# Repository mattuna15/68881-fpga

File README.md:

# MC68881/2 FPGA Core

## Overview
A VHDL implementation of a Motorola MC68881/MC68882-compatible floating-point
coprocessor targeting Xilinx 7-series and UltraScale+ FPGAs. The design implements
the full MC68881 instruction set including all arithmetic, transcendental,
program-control, system-control, and packed-decimal operations. It uses
DSP-pipelined sequential FP units for the core arithmetic datapath with
multi-cycle path constraints for timing closure at 50 MHz.

Hardware-verified on an Alinx AXU3EG board (Zynq UltraScale+ ZU3EG) via the
AXI4-Lite wrapper at 100 MHz bus / 50 MHz FPU, with end-to-end tests covering
arithmetic, transcendental, exponential, and logarithmic operations.

## Features
- **Full instruction set**: FADD, FSUB, FMUL, FDIV, FSQRT, FMOD, FREM, FSCALE,
  FSGLDIV, FSGLMUL, FABS, FNEG, FINT, FINTRZ, FGETEXP, FGETMAN, FTST, FCMP.
- **Lite mode** (`fpu_lite_g => true`): MC68040 hardware subset -- keeps 11 ALU
  ops (ADD/SUB/MUL/DIV/SQRT/CMP/ABS/NEG/INT/INTRZ/TST) plus control/move ops.
  Removes trig engine, sglops unit, and modrem post-processing via VHDL generate
  blocks; stubs out GETEXP/GETMAN inline. Estimated ~57-60% LUT savings (pending
  synthesis verification). Unsupported ops return zero in 1 cycle.
- **Transcendental engine**: FSIN, FCOS, FTAN, FSINCOS, FASIN, FACOS, FATAN,
  FATANH, FSINH, FCOSH, FTANH, FETOX, FETOXM1, FTWOTOX, FTENTOX, FLOGN,
  FLOGNP1, FLOG2, FLOG10. BRAM coefficient ROM with Horner polynomial
  evaluation, table-assisted range reduction (ATAN, LOG), Cody-Waite
  argument reduction (trig), and FPSP-derived 2^(J/64) EXP decomposition
  with minimax degree-6 polynomial.
- **Data movement**: FMOVE (all formats including packed decimal `.P`),
  FMOVEM (register lists and control registers), FMOVECR (ROM constants).
- **Program control**: FScc, FBcc, FDBcc, FTRAPcc, FNOP with BSUN trap gating.
- **MC68882 mode** (`fpu_version_g => FPU_68882`): Pin-compatible 68882 variant
  with larger FSAVE frames (idle $0038/14W, busy $00D4/53W), pending instruction
  pipeline (accepts a second cpGEN while the first is executing; auto-launches on
  completion), and NULL response during CIR_EXECUTE for reduced CPU stalls.
  FRESTORE accepts both 68881 and 68882 format words for migration compatibility.
  Default is FPU_68881 for backward compatibility.
- **System control**: FSAVE/FRESTORE with Null/Idle/Busy frame support (45-word
  68881 / 53-word 68882 Busy frame with full sub-unit save/restore hierarchy).
- **IEEE 754 compliance**: NaN propagation (SNaN/QNaN discrimination, payload
  preservation), infinity handling, signed zero, gradual underflow, all four
  rounding modes (nearest, zero, +inf, -inf), single/double/extended precision.
- **Exception handling**: Per-operation FPSR exception policies, FPCR trap
  enable, accrued exception accumulation.
- **Dual host interface**: Two operating modes over the same 5-bit address space:
  - **CIR dialog** -- authentic AN-947 coprocessor protocol with internal FP register
    file, hardware format conversion, and command/response/operand dialog (for M68020/030)
  - **Peripheral (register-mapped)** -- direct OPA/OPB/OPSEL/RES register access for
    any host CPU (ARM, RISC-V, soft-core) as a standalone FPU compute engine
  - Mode selected by writing bit 0 of address 13 (1=CIR, 0=peripheral); CIR is
    default on reset, matching real MC68881 behaviour
- **SoC wrappers**: AXI4-Lite and Wishbone B4 slave wrappers with clock domain
  crossing (toggle handshake CDC), DSACK timeout protection, and interrupt output.
  Enable direct integration into Xilinx AXI or RISC-V Wishbone SoC interconnects.

## Utilization (Xilinx Artix-7 200T, post-place)

| Resource | Full | Lite (`fpu_lite_g`) | Available | Full % | Lite % |
|----------|------|---------------------|-----------|--------|--------|
| Slice LUTs | 59,919 | 37,380 | 133,800 | 44.78% | 27.94% |
| Registers | 14,087 | 7,030 | 267,600 | 5.26% | 2.63% |
| Block RAM | 10.5 tiles | 0 | 365 | 2.88% | 0% |
| DSP48E1 | 34 | 18 | 740 | 4.59% | 2.43% |

*Non-incremental synthesis + implementation, Vivado 2025.2, `xc7a200tfbg676-1`. Date: 2026-03-27.
50 MHz target clock. MC68882 mode enabled (`fpu_version_g => FPU_68882`). Includes
FPSP-derived EXP 2^(J/64) decomposition with minimax degree-6 polynomial (EXPTBL
64-entry BRAM), LOG reciprocal table (avoids FP division), TWOTOX/TENTOX direct
reduction, table-assisted ATAN/LOG, Cody-Waite trig, CIR coprocessor interface,
full exception dialog paths, undocumented FMOVECR ROM constants, pending instruction
pipeline, and graphics framebuffer support. Lite figures are from 2026-03-21 (pre-
efficiency changes, trig engine excluded by generate block).*

### Timing
- Target clock: **50 MHz** (20.0 ns period) — 2× the original MC68881 max (25 MHz).
- Multi-cycle path constraints on sequential FP units, trig engine hold states,
  format conversion paths (operand staging, MOVE dispatch, LOG exponent conversion,
  FP register file to exception destinations).
- Packed decimal encode pipeline: 3-stage split (exponent extraction → DSP multiply
  → scale computation) with pipelined DSP48E1 input.
- Post-route WNS: **+0.272 ns** at 50 MHz (timing met). No hold violations.

### Target device compatibility
The design fits on several FPGA families. With `fpu_lite_g => true` (MC68040
hardware subset: 11 ALU ops, no trig/sglops/modrem), the core uses 37,380 LUTs
/ 18 DSPs / 0 BRAM:

| Device | LUTs | DSPs | Full fit? | Lite fit? |
|--------|------|------|-----------|-----------|
| Xilinx Artix-7 200T | 133,800 | 740 | Yes (45%) | Yes (28%) |
| Xilinx Artix-7 100T | 63,400 | 240 | Tight (95%) | Yes (59%) |
| Xilinx Zynq UltraScale+ ZU3EG | ~71,000 | 360 | Yes (~84%) | Yes (~53%) |
| Intel Cyclone V 5CEBA7 | 150,720 ALMs | 156 | Yes | Yes |
| Intel Cyclone V SE 5CSEBA6 (MiSTer DE10-Nano) | 41,910 ALMs | 112 | No (~75%) | Yes (~45%) |

All RTL is VHDL-93 compatible and vendor-portable (inferred DSP/BRAM, no Xilinx
IP cores). The source is VHDL-93 compatible (verified via `ghdl --std=93`) and
should synthesize directly in Quartus 17+ (as used by MiSTer). Verify with `scripts/check_vhdl93.sh`.
Porting requires XDC-to-SDC constraint conversion and minor DSP inference
adjustments.

**MiSTer note:** The DE10-Nano's Cyclone V SE has 41,910 ALMs (each ALM roughly
maps to 2 Xilinx LUTs, giving ~84K LUT-equivalent). The full FPU (60K LUTs /
34 DSPs) exceeds ALM capacity but fits within the 112 DSP budget. Lite mode
(37K LUTs ≈ ~19K ALMs, 18 DSPs, 0 BRAM) should fit comfortably. These are rough
estimates; actual Quartus ALM counts may differ from Xilinx LUT counts due to
architectural differences.

## Architecture

```
mc68881_top                     Bus interface, format converters, FMOVECR ROM
├── alu_inst (mc68881_alu)      Opcode dispatch, shared FP unit mux
│   ├── trig_inst               Transcendental engine (generate: not fpu_lite)
│   ├── divrem_inst             Radix-4 SRT division, FSQRT
│   │   └── modrem_post         FMOD/FREM post-processing (generic: enable_modrem_post)
│   ├── sglops_inst             FSCALE, FSGLDIV, FSGLMUL (generate: not fpu_lite)
│   ├── alu_mul_inst            Shared 64×64 sequential multiplier (DSP48E1 cascade)
│   └── alu_add_inst            Shared 67-bit sequential adder/subtractor
└── packed_unit_inst            Packed-decimal BCD encode/decode (uses shared mul/add)
```

The ALU dispatches to **exactly one** consumer at a time. The trig unit runs
concurrently and has its own dedicated FP units. The ALU's mul and add instances
are **shared** between the ALU's own FADD/FSUB/FMUL path, the modrem post-processing
path, and the packed-decimal unit — saving ~5,300 LUTs and 32 DSPs vs. dedicated
instances per consumer.

## Repository layout
- `src/` — RTL sources (10 files, ~11.4K lines)
  - `mc68881_pkg.vhd` — Types, constants, FP80 utility functions
  - `mc68881_top.vhd` — Top-level bus interface, format converters
  - `mc68881_alu.vhd` — ALU dispatcher, shared FP unit routing
  - `mc68881_trig_unit.vhd` — Transcendental engine (BRAM seed tables)
  - `mc68881_divrem_unit.vhd` — Division, square root, mod/rem
  - `mc68881_modrem_post_unit.vhd` — FMOD/FREM post-processing
  - `mc68881_fp80_mul_unit.vhd` — Sequential 64×64-bit FP80 multiplier
  - `mc68881_fp80_addsub_unit.vhd` — Sequential 67-bit FP80 adder/subtractor
  - `mc68881_sgl_ops_unit.vhd` — FSCALE, FSGLDIV, FSGLMUL
  - `mc68881_packed_decimal_unit.vhd` — Packed-decimal BCD conversion
- `wrappers/` — SoC bus wrappers
  - `mc68881_bus_bridge.vhd` — CDC toggle-handshake bridge + M68K bus cycle FSM
  - `mc68881_axilite_wrapper.vhd` — AXI4-Lite slave (instantiates bridge + FPU)
  - `mc68881_wishbone_wrapper.vhd` — Wishbone B4 slave (instantiates bridge + FPU)
  - `mc68881_wrapper.xdc` — ASYNC_REG + false path timing constraints for CDC bridge
  - `mc68881_ooc_timing.xdc` — Multicycle path constraints for OOC block design synthesis
- `src/vitis/` — Bare-metal C test apps for Xilinx Vitis (AXI-Lite hardware validation)
  - `mc68881_smoke_test.c` — Register read/write connectivity test (FPCR, FPIAR)
  - `mc68881_fsin_test.c` — FSIN computation test (sin(1.0), sin(0.0))
  - `mc68881_e2e_test.c` — End-to-end test with 15 vectors from GHDL testbench
- `validation/NeXT-68040/` — NeXT 68040LC system emulator (Turbo ROM boot, interactive `NeXT>` monitor, hardware FPU via FSAVE/FRESTORE frame translation, DisplayPort output)
- `validation/hello_world/` — M68K emulator + hardware FPU validation (Musashi, F-line trapping, ROM boot, USB keyboard)
- `validation/kicad/` — Validation PCB: MC68SEC000 + QMTECH Artix-7 + original MC68881FN (KiCad 8, Gerbers in `output/`)
- `src/vitis/roms/` — 68000 BIOS ROM source (assembler, disassembler, monitor with FPU support)
- `tb/` — VHDL-2008 self-checking testbenches (14 files, ~8.5K lines)
- `docs/` — Implementation plan, timing notes, reference documentation
- `verilog/` — Auto-generated Verilog conversion; `verilog/fpu_lite/` has the lite-mode variant (see [verilog/README.md](verilog/README.md))
- `scripts/` — Test runner, golden vector generator, implementation TCL
- `.github/workflows/ghdl.yml` — CI: GHDL analysis + 4 testbench runs
- `.githooks/pre-push` — Pre-push GHDL regression gate

## Running simulations
Use a VHDL-2008 capable simulator (GHDL 5.1.1+ recommended). The repo includes
a test script that runs the full regression suite:

```powershell
scripts/run_tests.ps1
```

The script uses `GHDL_EXE` if set, otherwise defaults to
`C:\code\ghdl-mcode-5.1.1-mingw64\bin\ghdl.exe` and finally `ghdl` on PATH.

### CI testbenches
The GitHub Actions workflow runs these testbenches on every push:
- `tb_mc68881_alu` — Arithmetic, NaN/infinity, transcendental, special values
- `tb_mc68881_alu_lite` — Lite-mode (`fpu_lite => true`): kept ops + removed ops return zero
- `tb_mc68881_top` — Bus interface, format conversions, FPSR/exception checks
- `tb_mc68881_ea_cycles` — Effective address cycle count tables
- `tb_mc68881_cycle_counts` — Instruction cycle timing verification

### Golden vectors
- Generator: `scripts/gen_golden_vectors.py` (mpmath-based FP80 rounded constants).
- Checked-in package: `tb/mc68881_golden_vectors_pkg.vhd`.
- Compile order: `mc68881_golden_vectors_pkg.vhd` must be analyzed before `tb_mc68881_alu.vhd`.

### Pre-push hook
The pre-push hook in `.githooks/pre-push` runs GHDL analysis and the ALU/top
testbenches. To enable hooks locally:

```sh
git config core.hooksPath .githooks
```

## Synthesis and LUT reporting
Use non-incremental synthesis for area/LUT comparisons. Incremental reuse can mask
RTL changes and produce stale utilization numbers.

```tcl
set_property AUTO_INCREMENTAL_CHECKPOINT 0 [get_runs synth_1]
set_property INCREMENTAL_CHECKPOINT "" [get_runs synth_1]
reset_run synth_1
launch_runs synth_1
```

For hotspot analysis, generate hierarchical utilization from the synthesized checkpoint:

```tcl
open_checkpoint mc68881_top.dcp
report_utilization -hierarchical -hierarchical_depth 10 -file mc68881_top_util_hier.rpt
```

### Transcendental accuracy
The transcendental engine achieves 30–64 bits of accuracy across operations,
verified by the torture testbench (357 self-checking tests):

| Operation | Typical accuracy | Method |
|-----------|-----------------|--------|
| SIN, COS, TAN | 30–40 bits | Cody-Waite argument reduction, table-assisted seed refinement |
| ASIN, ACOS, ATAN | 55–62 bits | Table-assisted polynomial (64 BRAM entries) |
| EXP, ETOXM1 | ~40–54 bits | FPSP 2^(J/64) decomposition, minimax degree-6 Horner |
| TWOTOX, TENTOX | ~47 bits | Direct k=nint(x) reduction, degree-9 Taylor |
| LOG, LOG2, LOG10 | ~54 bits | Table-assisted range reduction, reciprocal multiply |
| SINH, COSH | 30–50 bits | Dedicated odd/even Taylor polynomials |
| TANH | ~32–42 bits | Via EXP64 pipeline |

## Transcendental architecture guardrails
- The transcendental engine uses BRAM-style synchronous reads via
  `ST_SEED_READ -> ST_SEED_READ_WAIT -> ST_SEED_READ_LATCH`.
- Coefficient BRAM ROM stores 6 sets × 10 coefficients (EXP/LOG/ATAN/SINH/COSH/EXP64);
  requires 2-cycle read latency: `POLY_INIT` → `INIT_WAIT` → `MUL_PREP`.
- EXP64 BRAM (64 entries of 2^(J/64)) uses same synchronous read pattern:
  `ST_EXP64_N_POST` → `ST_EXP64_TABLE_WAIT` → `ST_EXP64_TABLE_LATCH`.
- LOG reciprocal table (64 entries of 1/c_i) reads alongside c_i and ln(c_i)
  on the same BRAM address — no extra read cycle needed.
- Do **not** replace synchronous reads with combinational table indexing — it
  breaks BRAM inference and increases LUT usage sharply.
- Validate architecture changes with non-incremental synth utilization reports.

## Verilog conversion
The VHDL sources can be converted to Verilog via `ghdl --synth` for use with
Verilator or other Verilog-only toolchains. The pre-push hook regenerates these
automatically. To convert manually:

```powershell
powershell -ExecutionPolicy Bypass -File scripts/convert_to_verilog.ps1
```

Output goes to [`verilog/`](verilog/). A lite-mode variant (`fpu_lite_g => true`)
is also generated into `verilog/fpu_lite/`. **These files are supplied as-is for
information only — no guarantee of correctness is made and no tests are run on
the converted code.** The VHDL sources remain the authoritative implementation.

## Block design integration (Xilinx Vivado)

The AXI-Lite wrapper can be added to a Vivado block design as a custom RTL module.
Both XDC constraint files must be included with the IP:

- `mc68881_wrapper.xdc` — CDC false paths for the toggle-handshake bridge
- `mc68881_ooc_timing.xdc` — Multicycle path constraints scoped to `*/u_fpu/`

The OOC timing constraints are adapted from `mc68881_top.xdc` for the wrapper
hierarchy. Key differences from standalone synthesis:
- All `get_pins` patterns use `*/u_fpu/` prefix
- `move_cfg_decoded_reg` (record type) is optimized away in OOC synthesis;
  constraints target `move_cfg_reg_reg` instead
- `packed_unit_inst` is inside generate block `packed_engine_full_g`
- CDC `get_cells` filters include `&& IS_SEQUENTIAL` to avoid matching LUT cells

Verified on Xilinx Zynq UltraScale+ ZU3EG (AXU3EG board) with Vivado 2025.2:
post-route WNS **+1.186 ns** at 100 MHz AXI / 50 MHz FPU (MC68882 mode).
Board design utilization: 64,014 LUTs (91%), 15,206 registers, 8 BRAM tiles,
34 DSPs. All timing constraints met with no hold violations.

### Vitis hardware test apps

The `src/vitis/` directory contains standalone C test applications for
validating the FPU over AXI-Lite. These target the Xilinx Vitis bare-metal BSP.

| Test | What it checks |
|------|----------------|
| `mc68881_smoke_test.c` | Bus connectivity: write/readback of FPCR and FPIAR |
| `mc68881_fsin_test.c` | FPU operation: sin(1.0) and sin(0.0) with result printout |
| `mc68881_e2e_test.c` | 17 test vectors: ADD, SUB, MUL, DIV, SQRT, SIN, COS, TAN, ETOX, LOGN, FMOVECR, pi/3 |

All tests include `0xFFFFFFFF` bus fault detection, timeout handling with status
reporting, and non-zero exit on failure for use in automated test flows.

Set `MC68881_BASE` to match your address map (default `0x80000000`).

### M68K emulator validation (CIR + peripheral modes)

The [`validation/hello_world/src/README.md`](validation/hello_world/src/README.md) project runs a full
M68K emulator (Musashi) on the ARM core, trapping F-line FPU instructions and
executing them on the hardware FPU over AXI-Lite. The test suite validates
**both** operating modes:

**Peripheral mode** (7 + 5 tests) -- the FPU as a standalone compute engine.
The emulator's F-line handler converts operands to FP80 in software, writes them
to the OPA/OPB registers, triggers execution via OPSEL, and reads results from
RES. No CIR involvement:

```c
fpu_wr(OFF_CIR_MODE, 0);              // ensure peripheral mode
fpu_load_opa(a);                       // write FP80 operand A
fpu_load_opb(b);                       // write FP80 operand B
fpu_wr(OFF_OPSEL, OPSEL(FPOP_ADD));   // trigger FADD
while (!(fpu_rd(OFF_STATUS) & 1)) {}  // poll for completion
result = fpu_read_res();               // read FP80 result
```

**CIR dialog mode** (7 tests) -- the authentic AN-947 coprocessor protocol.
The host writes a Command + OpWord to start a dialog, the FPU responds with
transfer primitives, the host feeds operand words through the CIR Operand
register, and the FPU stores results in its internal FP register file (FP0-FP7):

```c
cir_wr(OFF_CIR_RESPONSE, 1);           // ensure CIR mode
cir_wr(OFF_CIR_COMMAND, cmd);          // operation + format + register
cir_wr(OFF_CIR_OPWORD,  CIR_OPWORD_CPGEN);  // triggers FSM
resp = cir_poll_response();            // → 0x9604 (AN-947: transfer CPU→FPU, 4 bytes)
cir_wr(OFF_CIR_OPERAND, 42);          // write source operand
cir_wait_null();                       // dialog complete; result in FP register
```

The two modes share a 5-bit address space with overlapping registers (addresses
1, 4, 5, 7, 8, 14). A mode flag at address 13 gates the decode: CIR mode is
default on reset. See the [validation README](validation/hello_world/src/README.md)
for the full address map, protocol details, and code examples.

19/19 tests pass: 7 peripheral smoke + 7 CIR dialog + 5 Musashi integration.

### BIOS ROM boot mode

The default build boots a 68000 BIOS ROM with an interactive monitor, built-in
assembler (CODE68K), and disassembler (DCODE68K). Character I/O is routed through
MC68901 MFP emulation (ARM UART ↔ emulated MFP USART) and rendered to a text
framebuffer displayed on the PS DisplayPort output (1280×720@60Hz).

USB keyboards and mice are supported via the ZynqMP DWC3 xHCI host controller:
- **Keyboard**: HID boot-protocol, Caps Lock/Num Lock with LED feedback, feeds
  ASCII into the MFP RX buffer alongside ARM UART input
- **Mouse**: HID boot-protocol, buttons + relative/absolute position tracking,
  accessible via memory-mapped I/O at `$FD0050` and TRAP #15 (D0=26/27/28)
- Automatic hub traversal (up to 3 levels) — works with keyboards and mice
  behind USB hubs, including combo devices with built-in hubs

The assembler and disassembler support all MC68881 FPU instructions:
- **39 FPU mnemonics**: FMOVE through FMOVECR (all arithmetic, transcendental,
  data movement, and compare/test operations)
- **32 FBcc conditions**: FBEQ, FBGT, FBGE, FBLT, FBLE, FBGL, FBGLE, FBOGT,
  FBOGE, FBOLT, FBOLE, FBOGL, FBOR, FBUN, FBUEQ, FBUGT, FBUGE, FBULT,
  FBULE, FBNE, FBT, FBSF, FBST, FBSEQ, FBSNE, and negated variants
- **All format suffixes**: `.B`, `.W`, `.L`, `.S`, `.D`, `.X`, `.P`
- **Floating-point literals**: Decimal FP constants (e.g., `FADD.S #2.35,FP0`)
  with IEEE 754 conversion for `.S` (single), `.D` (double), and `.X` (extended)
- **FMOVE variants**: reg↔reg, mem↔reg, reg→mem, FMOVECR, FMOVE to/from
  FPCR/FPSR/FPIAR

The monitor supports Go (execute), single-step Trace, software Breakpoints
(up to 8), register dump (CPU + FPU), and memory inspect/modify. See the
[BIOS User Guide](docs/merlin2_bios.md) for full command reference and build
instructions.

The BIOS ROM source is in `validation/hello_world/src/roms/bios.s`. Build with:

```bash
vasmm68k_mot -Fbin -m68000 -o bios.bin bios.s
# Extract ROM section and convert to C header (see docs/merlin2_bios.md)
```

### Hardware validation output

E2e test run on AXU3EG (Zynq UltraScale+ ZU3EG), Vitis 2025.2:

```
Zynq MP First Stage Boot Loader
Release 2025.2   Mar  9 2026  -  17:13:45
PMU-FW is not running, certain applications may not be supported.
PMU Firmware 2025.2     Mar  9 2026   17:13:51
PMU_ROM Version: xpbr-v8.1.0-0

mc68881 e2e test (vectors from GHDL tb)
========================================
PASS ADD 3.7+2.4
PASS SUB -2.3-0.6
PASS MUL 3.7*2.4
PASS DIV 12.5/-0.7
PASS SQRT(9)
PASS SIN(1.0)
PASS SIN(1.1)
PASS SIN(-0.7)
PASS COS(-2.3)
PASS COS(0.3)
PASS TAN(0.9)
PASS ETOX(0.75)
PASS LOGN(1.25)
PASS SIN(0)
PASS SQRT(1)
PASS FMOVECR(pi)
PASS DIV(pi/3)
========================================
17 passed, 0 failed, 17 total
ALL TESTS PASSED
```

### FPU benchmarks

Standard floating-point benchmarks run on the M68K emulator with hardware FPU
(F-line trapping to FPGA), measured on AXU3EG at 100 MHz AXI / 50 MHz FPU:

**Whetstone** (NLOOP=10, exercises ADD/SUB/MUL/DIV/SQRT/SIN/COS/ATAN/LOG/EXP):
```
=== Whetstone Benchmark ===
M2 (array)... OK
M3 (proc array)... OK
M4 (conditionals)... OK
M6 (log/exp/sqrt)... OK
M7 (proc calls)... OK
M8 (trig)... OK

Passes: 10
Elapsed: 2191 ms
KWIPS: 4564
Whetstone complete.
```

**Savage** (2500 iterations of x = tan(atan(exp(ln(sqrt(x*x)))))), result should be 1.0):
```
=== Savage Benchmark ===
Result: 3FFE0000 FFFFFFFF FFFE54C8
Expect: 3FFF0000 80000000 00000000  (1.0)
Iterations: 2500
Elapsed: 210 ms
Done.
```

The Savage result (~0.999999999999994) shows ~6×10⁻¹⁵ accumulated rounding error
over 2500 iterations of 6 chained transcendental operations — reasonable for
64-bit extended precision.

Benchmark sources are in `validation/hello_world/src/roms/` (`savage.s`, `whetstone.s`).

### GCC example programs

The `toolchain/examples/` directory contains C programs compiled with the m68k-elf-gcc
cross-compiler and loaded via S-record transfer. Build with `.\build.ps1` (requires
Cygwin with m68k-elf-gcc).

| Program | Description | FPU? |
|---------|-------------|------|
| `hello.c` | Hello world (printf, TRAP I/O) | No |
| `fputest.c` | FPU arithmetic test (sin, cos, sqrt) | Yes |
| `fireworks.c` | Animated fireworks demo (physics + graphics) | Yes |
| `rtctest.c` | RTC date/time read/set, Timer C tick monitor | No |
| `mousetest.c` | USB mouse demo (crosshair cursor, click markers) | No |

**Mouse demo** (`mousetest.c`): Switches to 1280×720 graphics mode and renders a
green crosshair cursor that tracks the USB mouse. Left/right/middle clicks leave
coloured dot markers on the screen. A banner at the top displays the current X/Y
position and active buttons. Press any keyboard key to exit. Reads mouse state
directly from memory-mapped I/O at `$FD0050` (buttons, delta, absolute position).

## Validation PCB

The `validation/kicad/` directory contains a KiCad 8 project ("NextCuboid") for a
physical validation board that connects a real MC68SEC000 CPU to the QMTECH
Artix-7 200T core board running the FPGA FPU core, alongside an original 5V
MC68881FN for comparison testing. This is the first physical hardware validation
of the coprocessor interface — exercising real bus timing, level shifting, and
the CIR dialog protocol over actual copper.

### Board architecture

```
MC68SEC000FU20 (3.3V, 20 MHz)
    │
    ├── Coprocessor bus ──► SN74LVC8T245 level shifters (3.3V ↔ 5V)
    │                           │
    │                           ├──► MC68881FN (original 5V DIP/PLCC)
    │                           │
    │                           └──► QMTECH Artix-7 200T (mc68881_top)
    │
    └── Active-low control ──► 74LVC1G125 single-gate buffers
```

### Key components

| Component | Part | Role |
|-----------|------|------|
| CPU | MC68SEC000FU20 | 3.3V 68000-compatible bus master |
| FPGA FPU | QMTECH XC7A200T core board | Runs `mc68881_top` with bus bridge |
| Reference FPU | MC68881FN (original Motorola) | 5V DIP/PLCC, golden reference |
| Level shifters | SN74LVC8T245 (×5) | Bidirectional 3.3V ↔ 5V translation |
| Control buffers | 74LVC1G125 (×2) | Single-gate active-low signal translation |

The board uses dual QMTECH connectors (active main + active secondary headers)
and includes 4.7K pull-up resistors on open-drain/open-collector signals plus
100nF decoupling capacitors on all ICs. Gerber outputs are in
`validation/kicad/output/`.

PCB production sponsored by [PCBWay](https://www.pcbway.com) — thanks to them
for supporting this project.

## Status
All checklist items complete. See `docs/fpu-progress-checklist.md` for history.

## Documentation index

### Project documentation
| File | Description |
|------|-------------|
| [`docs/history.md`](docs/history.md) | Development history and changelog |
| [`docs/merlin2_bios.md`](docs/merlin2_bios.md) | Merlin2 BIOS monitor user guide |
| [`docs/trig_design.md`](docs/trig_design.md) | Transcendental engine architecture and algorithm design |
| [`docs/fpsp_comparison_checklist.md`](docs/fpsp_comparison_checklist.md) | FPSP (68040 FP software package) comparison checklist |
| [`docs/next68040_defect_checklist.md`](docs/next68040_defect_checklist.md) | NeXT 68040LC emulator defect/TODO tracker |
| [`docs/nextmach_boot_checklist.md`](docs/nextmach_boot_checklist.md) | NeXTMach kernel boot checklist |
| [`docs/merlin2_tasklist.md`](docs/merlin2_tasklist.md) | Merlin2 BIOS task list |
| [`docs/archive/fpu-progress-checklist.md`](docs/archive/fpu-progress-checklist.md) | Master checklist: implementation status (archived) |
| [`docs/archive/fmovecr_qemu_summary.md`](docs/archive/fmovecr_qemu_summary.md) | FMOVECR ROM constant cross-reference (archived) |
| [`docs/archive/qmtech_constraints_verification.md`](docs/archive/qmtech_constraints_verification.md) | XDC constraints verification for QMTECH board (archived) |

### Motorola / Atari reference manuals
| File | Description |
|------|-------------|
| [`docs/datasheets/MC68881UM.pdf`](docs/datasheets/MC68881UM.pdf) | MC68881/MC68882 User Manual (Motorola) |
| [`docs/datasheets/MC68881.PDF`](docs/datasheets/MC68881.PDF) | MC68881 datasheet |
| [`docs/datasheets/MC68040UM.pdf`](docs/datasheets/MC68040UM.pdf) | MC68040 User Manual (Motorola) |
| [`docs/datasheets/68881-tech-summary.pdf`](docs/datasheets/68881-tech-summary.pdf) | MC68881 Technical Summary |
| [`docs/datasheets/AN-0947_MC68881...pdf`](docs/datasheets/AN-0947_MC68881_Floating-Point_Coprocessor_as_a_Peripheral_in_a_M68000_System_%5BMotorola_1987_37p%5D.pdf) | AN-947: MC68881 as Peripheral in M68000 System |
| [`docs/datasheets/68881-programming.txt`](docs/datasheets/68881-programming.txt) | MC68881 programming reference notes |
| [`docs/datasheets/atari_sfp_en.pdf`](docs/datasheets/atari_sfp_en.pdf) | Atari SFP-004 programming by example |
| [`docs/datasheets/atari_68881_co-processor.pdf`](docs/datasheets/atari_68881_co-processor.pdf) | Atari MC68881 coprocessor board reference |

### Hardware reference
| File | Description |
|------|-------------|
| [`docs/datasheets/AXU3EG_User_Manual.pdf`](docs/datasheets/AXU3EG_User_Manual.pdf) | Alinx AXU3EG (Zynq UltraScale+ ZU3EG) board manual |
| [`docs/datasheets/QMTECH_XC7A200T-CORE-BOARD-V01-*.pdf`](docs/datasheets/) | QMTECH Artix-7 200T core board manual |
| [`docs/datasheets/MecbManual.pdf`](docs/datasheets/MecbManual.pdf) | MECB 68000 educational board manual |

### Design plans
| File | Description |
|------|-------------|
| [`docs/plans/2026-03-22-68040-emutos-variant.md`](docs/plans/2026-03-22-68040-emutos-variant.md) | MC68040 EmuTOS variant plan |
| [`docs/plans/2026-03-19-68882-upgrade.md`](docs/plans/2026-03-19-68882-upgrade.md) | MC68882 upgrade plan (pending pipeline, frame formats) |
| [`docs/plans/2026-03-03-s7-coprocessor-interface.md`](docs/plans/2026-03-03-s7-coprocessor-interface.md) | CIR coprocessor interface implementation plan |
| [`docs/plans/2026-02-28-packed-decimal-completion.md`](docs/plans/2026-02-28-packed-decimal-completion.md) | Packed decimal conversion completion plan |

### READMEs
| File | Description |
|------|-------------|
| [`validation/NeXT-68040/README.md`](validation/NeXT-68040/README.md) | NeXT 68040LC emulator: Turbo ROM boot, interactive monitor, hardware FPU on ZynqMP |
| [`validation/hello_world/src/README.md`](validation/hello_world/src/README.md) | Validation firmware: peripheral + CIR protocol, SFP004 benchmark |
| [`toolchain/README.md`](toolchain/README.md) | M68K GCC cross-compilation toolchain |
| [`toolchain/merlin-68k-toolchain/README.md`](toolchain/merlin-68k-toolchain/README.md) | Merlin2 68K toolchain (newlib, BSP) |

## License
See repository for license terms.

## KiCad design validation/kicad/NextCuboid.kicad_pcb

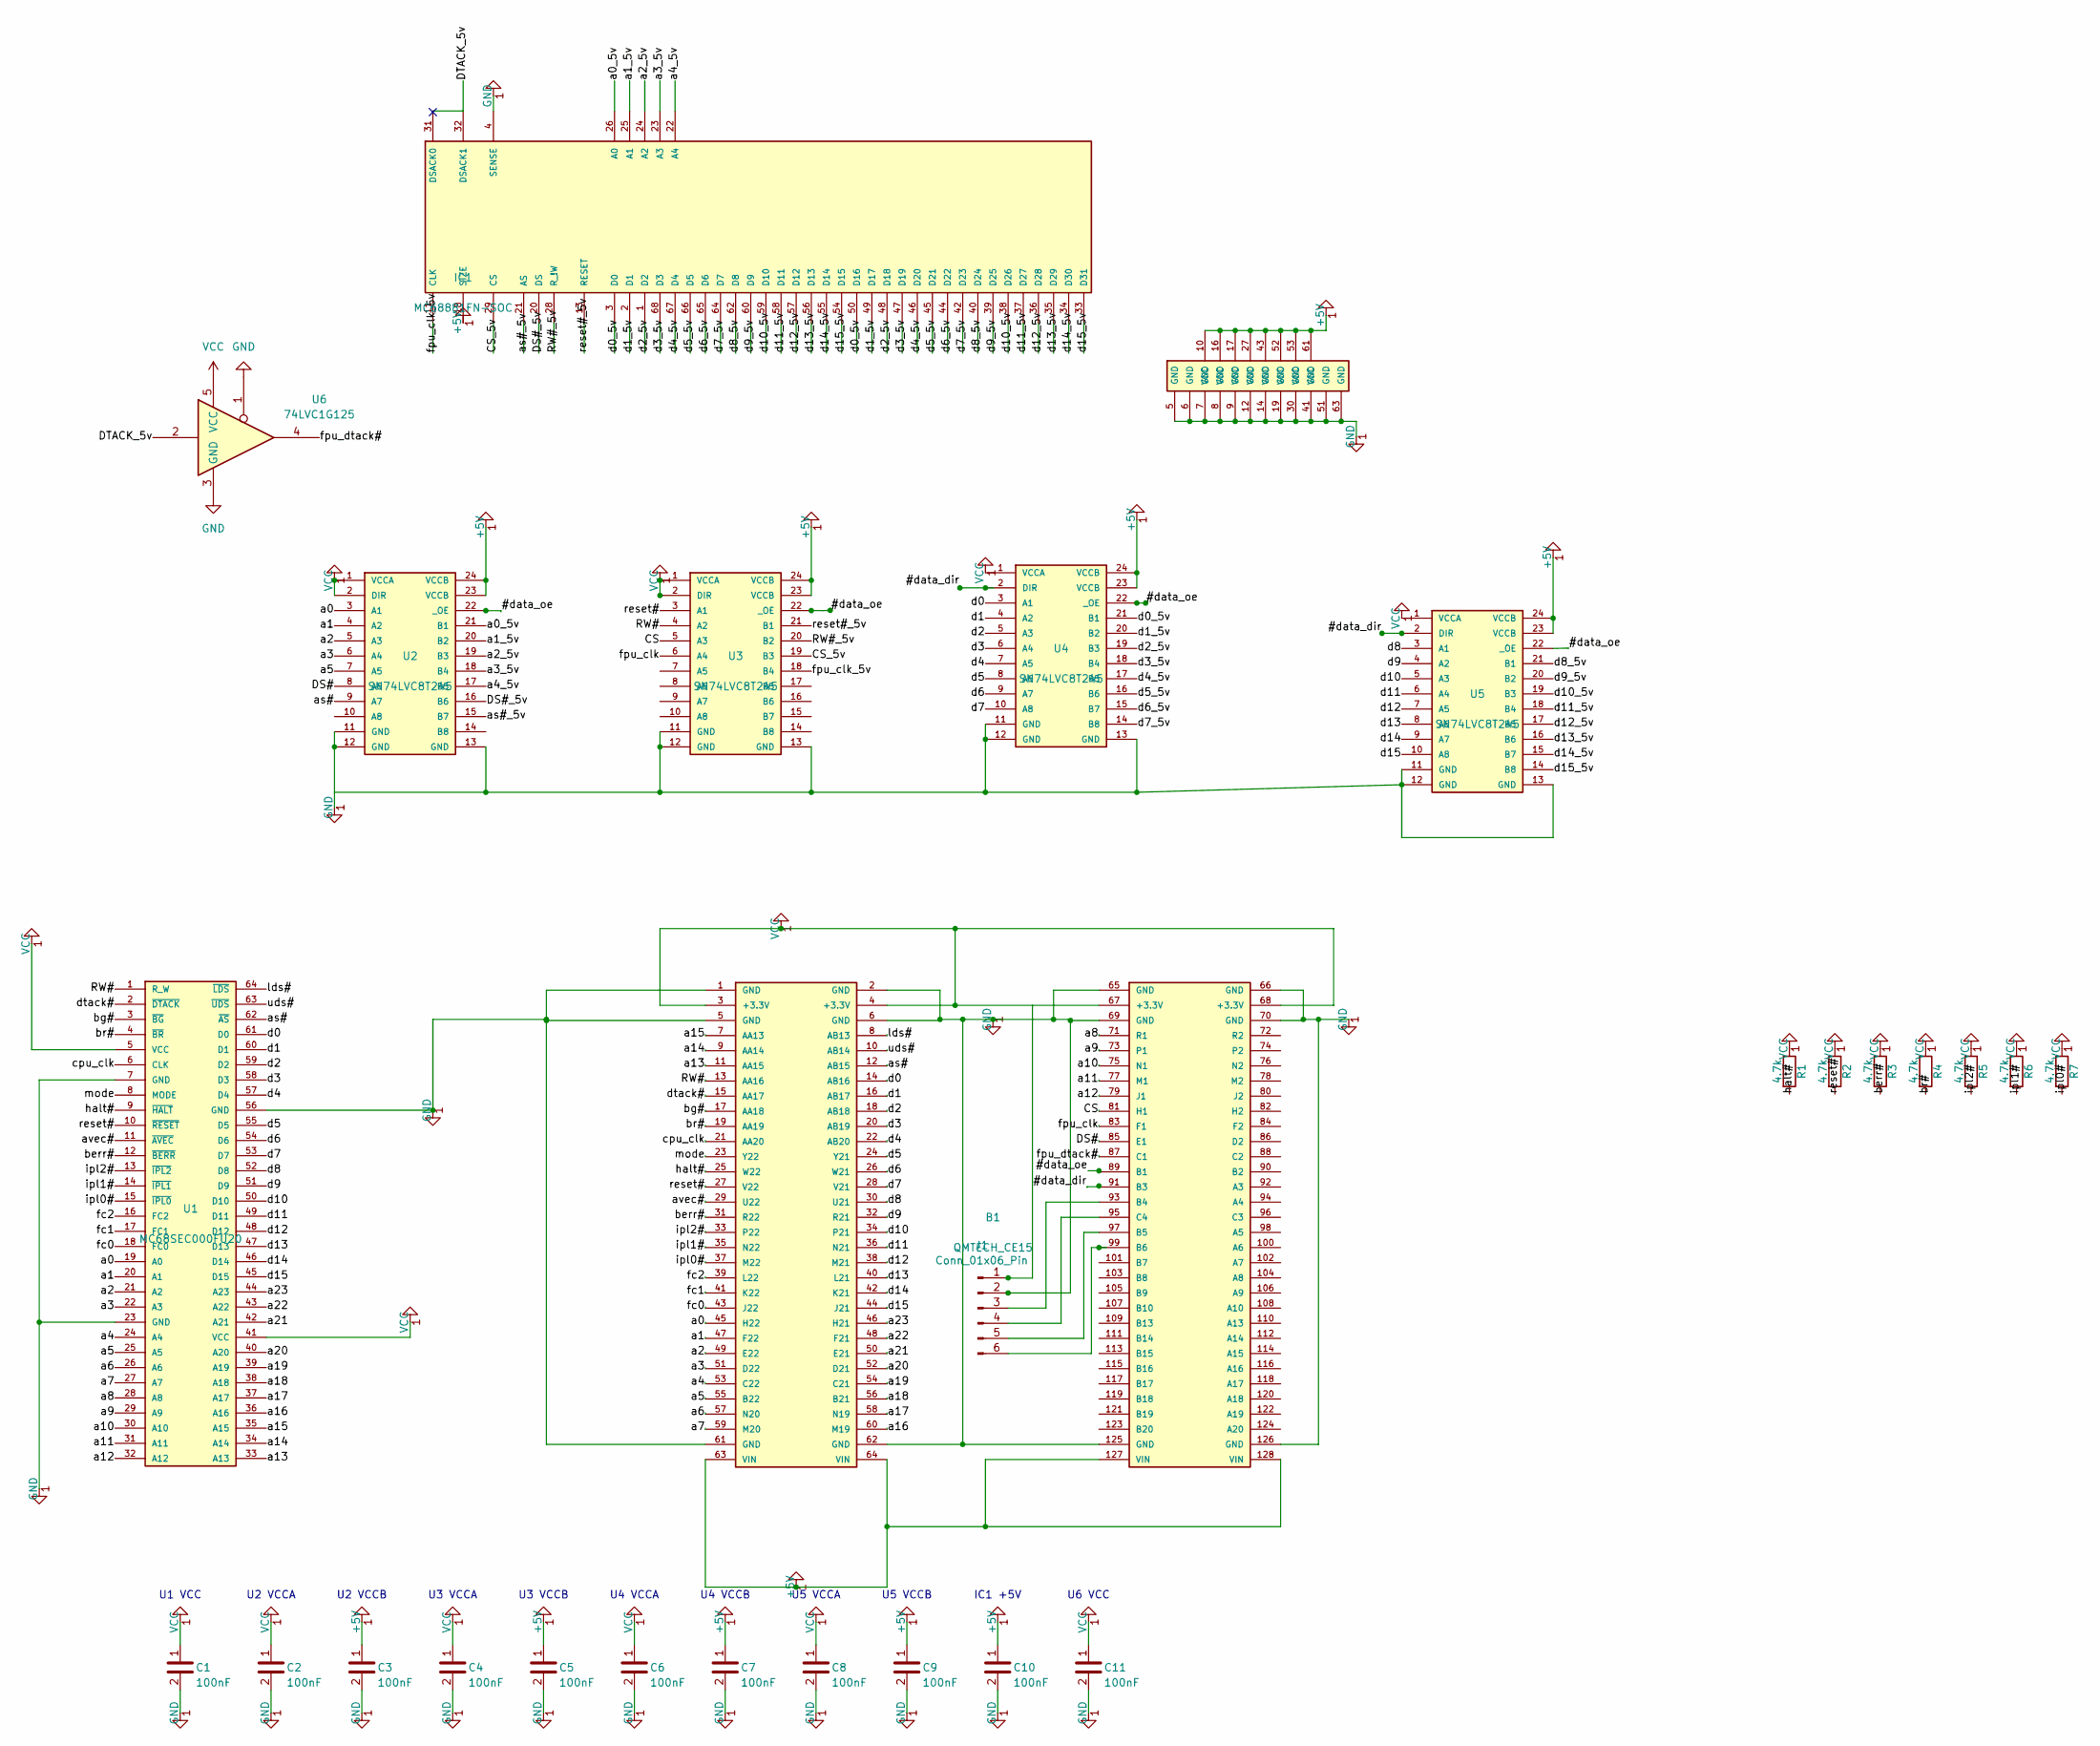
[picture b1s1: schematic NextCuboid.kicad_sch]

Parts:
B1: QMTECH_CE15; QMTECH_BOARD
C1, C2, C3, C4, C5, C6, C7, C8, C9, C10, C11: 100nF; C_Disc_D5.0mm_W2.5mm_P2.50mm
IC1: MC68881FN-SOC; PLCC68-S
J1: Conn_01x06_Pin; PinHeader_1x06_P2.54mm_Vertical
R1, R2, R3, R4, R5, R6, R7: 4.7k; R_Axial_DIN0207_L6.3mm_D2.5mm_P7.62mm_Horizontal
U1: MC68SEC000FU20; LQFP-64_L14.0-W14.0-P0.80-LS16.0-BL
U2, U3, U4, U5: SN74LVC8T245; DIP24L_BREAKOUT
U6: 74LVC1G125; SOT-23-5

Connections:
+5V: B1.63 (VIN), B1.64 (VIN), B1.127 (VIN), B1.128 (VIN), C3.1, C5.1, C7.1, C9.1, C10.1, IC1.10 (VCC), IC1.16 (VCC), IC1.17 (VCC), IC1.18 (SIZE), IC1.27 (VCC), IC1.43 (VCC), IC1.52 (VCC), IC1.53 (VCC), IC1.61 (VCC), U2.23 (VCCB), U2.24 (VCCB), U3.23 (VCCB), U3.24 (VCCB), U4.23 (VCCB), U4.24 (VCCB), U5.23 (VCCB), U5.24 (VCCB)
/#data_dir: U4.2 (DIR), U5.2 (DIR)
/#data_oe: B1.89 (B1), U2.22 (_OE), U3.22 (_OE), U4.22 (_OE), U5.22 (_OE)
/CS: B1.81 (H1), U3.5 (A3)
/CS_5v: IC1.29 (CS), U3.19 (B3)
/DS#: B1.85 (E1), U2.8 (A6)
/DS#_5v: IC1.20 (DS), U2.16 (B6)
/DTACK_5v: IC1.31 (DSACK0), IC1.32 (DSACK1), U6.2
/RW#: B1.13 (AA16), U1.1 (R_W), U3.4 (A2)
/RW#_5v: IC1.28 (R_!W), U3.20 (B2)
/a0: B1.45 (H22), U1.19 (A0), U2.3 (A1)
/a0_5v: IC1.26 (A0), U2.21 (B1)
/a1: B1.47 (F22), U1.20 (A1), U2.4 (A2)
/a1_5v: IC1.25 (A1), U2.20 (B2)
/a2: B1.49 (E22), U1.21 (A2), U2.5 (A3)
/a2_5v: IC1.24 (A2), U2.19 (B3)
/a3: B1.51 (D22), U1.22 (A3), U2.6 (A4)
/a3_5v: IC1.23 (A3), U2.18 (B4)
/a4: B1.53 (C22), U1.24 (A4)
/a4_5v: IC1.22 (A4), U2.17 (B5)
/a5: B1.55 (B22), U1.25 (A5), U2.7 (A5)
/a6: B1.57 (N20), U1.26 (A6)
/a7: B1.59 (M20), U1.27 (A7)
/a8: B1.71 (R1), U1.28 (A8)
/a9: B1.73 (P1), U1.29 (A9)
/a10: B1.75 (N1), U1.30 (A10)
/a11: B1.77 (M1), U1.31 (A11)
/a12: B1.79 (J1), U1.32 (A12)
/a13: B1.11 (AA15), U1.33 (A13)
/a14: B1.9 (AA14), U1.34 (A14)
/a15: B1.7 (AA13), U1.35 (A15)
/a16: B1.60 (M19), U1.36 (A16)
/a17: B1.58 (N19), U1.37 (A17)
/a18: B1.56 (B21), U1.38 (A18)
/a19: B1.54 (C21), U1.39 (A19)
/a20: B1.52 (D21), U1.40 (A20)
/a21: B1.50 (E21), U1.42 (A21)
/a22: B1.48 (F21), U1.43 (A22)
/a23: B1.46 (H21), U1.44 (A23)
/as#: B1.12 (AB15), U1.62 (~AS), U2.9 (A7)
/as#_5v: IC1.21 (AS), U2.15 (B7)
/avec#: B1.29 (U22), U1.11 (~AVEC)
/berr#: B1.31 (R22), R3.2, U1.12 (~BERR)
/bg#: B1.17 (AA18), U1.3 (~BG)
/br#: B1.19 (AA19), R4.2, U1.4 (~BR)
/cpu_clk: B1.21 (AA20), U1.6 (CLK)
/d0: B1.14 (AB16), U1.61 (D0), U4.3 (A1)
/d0_5v: IC1.3 (D0), IC1.50 (D16), U4.21 (B1)
/d1: B1.16 (AB17), U1.60 (D1), U4.4 (A2)
/d1_5v: IC1.2 (D1), IC1.49 (D17), U4.20 (B2)
/d2: B1.18 (AB18), U1.59 (D2), U4.5 (A3)
/d2_5v: IC1.1 (D2), IC1.48 (D18), U4.19 (B3)
/d3: B1.20 (AB19), U1.58 (D3), U4.6 (A4)
/d3_5v: IC1.47 (D19), IC1.68 (D3), U4.18 (B4)
/d4: B1.22 (AB20), U1.57 (D4), U4.7 (A5)
/d4_5v: IC1.46 (D20), IC1.67 (D4), U4.17 (B5)
/d5: B1.24 (Y21), U1.55 (D5), U4.8 (A6)
/d5_5v: IC1.45 (D21), IC1.66 (D5), U4.16 (B6)
/d6: B1.26 (W21), U1.54 (D6), U4.9 (A7)
/d6_5v: IC1.44 (D22), IC1.65 (D6), U4.15 (B7)
/d7: B1.28 (V21), U1.53 (D7), U4.10 (A8)
/d7_5v: IC1.42 (D23), IC1.64 (D7), U4.14 (B8)
/d8: B1.30 (U21), U1.52 (D8), U5.3 (A1)
/d8_5v: IC1.40 (D24), IC1.62 (D8), U5.21 (B1)
/d9: B1.32 (R21), U1.51 (D9), U5.4 (A2)
/d9_5v: IC1.39 (D25), IC1.60 (D9), U5.20 (B2)
/d10: B1.34 (P21), U1.50 (D10), U5.5 (A3)
/d10_5v: IC1.38 (D26), IC1.59 (D10), U5.19 (B3)
/d11: B1.36 (N21), U1.49 (D11), U5.6 (A4)
/d11_5v: IC1.37 (D27), IC1.58 (D11), U5.18 (B4)
/d12: B1.38 (M21), U1.48 (D12), U5.7 (A5)
/d12_5v: IC1.36 (D28), IC1.57 (D12), U5.17 (B5)
/d13: B1.40 (L21), U1.47 (D13), U5.8 (A6)
/d13_5v: IC1.35 (D29), IC1.56 (D13), U5.16 (B6)
/d14: B1.42 (K21), U1.46 (D14), U5.9 (A7)
/d14_5v: IC1.34 (D30), IC1.55 (D14), U5.15 (B7)
/d15: B1.44 (J21), U1.45 (D15), U5.10 (A8)
/d15_5v: IC1.33 (D31), IC1.54 (D15), U5.14 (B8)
/dtack#: B1.15 (AA17), U1.2 (~DTACK)
/fc0: B1.43 (J22), U1.18 (FC0)
/fc1: B1.41 (K22), U1.17 (FC1)
/fc2: B1.39 (L22), U1.16 (FC2)
/fpu_clk: B1.83 (F1), U3.6 (A4)
/fpu_clk_5v: IC1.11 (CLK), U3.18 (B4)
/fpu_dtack#: B1.87 (C1), U6.4
/halt#: B1.25 (W22), R1.2, U1.9 (~HALT)
/ipl0#: B1.37 (M22), R7.2, U1.15 (~IPL0)
/ipl1#: B1.35 (N22), R6.2, U1.14 (~IPL1)
/ipl2#: B1.33 (P22), R5.2, U1.13 (~IPL2)
/lds#: B1.8 (AB13), U1.64 (~LDS)
/mode: B1.23 (Y22), U1.8 (MODE)
/reset#: B1.27 (V22), R2.2, U1.10 (~RESET), U3.3 (A1)
/reset#_5v: IC1.13 (RESET), U3.21 (B1)
/uds#: B1.10 (AB14), U1.63 (~UDS)
GND: B1.1 (GND), B1.2 (GND), B1.5 (GND), B1.6 (GND), B1.61 (GND), B1.62 (GND), B1.65 (GND), B1.66 (GND), B1.69 (GND), B1.70 (GND), B1.125 (GND), B1.126 (GND), C1.2, C2.2, C3.2, C4.2, C5.2, C6.2, C7.2, C8.2, C9.2, C10.2, C11.2, IC1.4 (SENSE), IC1.5 (GND), IC1.6 (GND), IC1.7 (GND), IC1.8 (GND), IC1.9 (GND), IC1.12 (GND), IC1.14 (GND), IC1.19 (GND), IC1.30 (GND), IC1.41 (GND), IC1.51 (GND), IC1.63 (GND), J1.2, U1.7 (GND), U1.23 (GND), U1.56 (GND), U2.11 (GND), U2.12 (GND), U2.13 (GND), U3.11 (GND), U3.12 (GND), U3.13 (GND), U4.11 (GND), U4.12 (GND), U4.13 (GND), U5.11 (GND), U5.12 (GND), U6.1, U6.3 (GND)
unnamed: B1.93 (B4), J1.3
unnamed: B1.97 (B5), J1.5
unnamed: B1.99 (B6), J1.6
unnamed: B1.95 (C4), J1.4
VCC: B1.3 (+3.3V), B1.4 (+3.3V), B1.67 (+3.3V), B1.68 (+3.3V), C1.1, C2.1, C4.1, C6.1, C8.1, C11.1, R1.1, R2.1, R3.1, R4.1, R5.1, R6.1, R7.1, U1.5 (VCC), U1.41 (VCC), U2.1 (VCCA), U2.2 (DIR), U3.1 (VCCA), U3.2 (DIR), U4.1 (VCCA), U5.1 (VCCA), U6.5 (VCC)

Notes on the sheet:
U5 VCCA
U2 VCCB
U5 VCCB
IC1 +5V
U4 VCCB
U3 VCCB
U2 VCCA
U3 VCCA
U1 VCC
U4 VCCA
U6 VCC

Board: 4 copper layers, 27 parts (0 on the bottom side), 100 nets, no tracks yet.

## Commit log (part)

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2026-02-25 Fix FMOVE exception flow and FP format conversion semantics
2026-02-26 Fix FMOVE reg->mem overflow/underflow exception signaling
2026-02-26 Complete B6 conditional dialog ordering and BSUN trap gating
2026-02-27 impl: close trig MCP timing endpoint with aggressive route flow
2026-02-27 B8 phase: add packed-decimal transport and conversion slice
2026-03-02 Re-enable full packed decimal default with timed compact engine
2026-03-02 Fix GHDL CI compile order for packed decimal unit
2026-03-02 update project files
2026-03-08 update readme figures
2026-03-11 add .xsa
2026-03-11 Remove CIR feature gating information
    Removed CIR feature gating section from README.
2026-03-11 Update verilog
    Verilog conversion files
2026-03-11 Fix README path for hello_world project
    Corrected the path in the README for the hello_world project.
2026-03-11 Fix link formatting in README.md
2026-03-21 pcb and others
    first validation pcb
2026-03-23 Update emulation values
2026-03-24 Update project name to MC68881/2 FPGA Core
2026-03-27 update bug
